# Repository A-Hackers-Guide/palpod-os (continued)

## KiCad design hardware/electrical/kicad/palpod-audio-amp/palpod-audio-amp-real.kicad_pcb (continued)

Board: 6 copper layers, 73 parts (0 on the bottom side), 78 nets, no tracks yet.

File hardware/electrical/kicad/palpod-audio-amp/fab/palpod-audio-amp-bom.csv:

"Refs","Value","Footprint","Qty","DNP"
"A13","1ET7040SA_TWEETER","palpod-audio-amp:Purifi_1ET7040SA_Module","1",""
"A14","1ET7040SA_MID","palpod-audio-amp:Purifi_1ET7040SA_Module","1",""
"A15","1ET7040SA_WOOFER","palpod-audio-amp:Purifi_1ET7040SA_Module","1",""
"A16","1ET7040SA_SUBWOOFER","palpod-audio-amp:Purifi_1ET7040SA_Module","1",""
"C28","100nF","Capacitor_SMD:C_0402_1005Metric","1",""
"C29","100nF","Capacitor_SMD:C_0402_1005Metric","1",""
"C30","100nF","Capacitor_SMD:C_0402_1005Metric","1",""
"C31","100nF","Capacitor_SMD:C_0402_1005Metric","1",""
"C32","100nF","Capacitor_SMD:C_0402_1005Metric","1",""
"C33","100nF","Capacitor_SMD:C_0402_1005Metric","1",""
"C34","100nF","Capacitor_SMD:C_0402_1005Metric","1",""
"C35","100nF","Capacitor_SMD:C_0402_1005Metric","1",""
"C36","100nF","Capacitor_SMD:C_0402_1005Metric","1",""
"C37","100nF","Capacitor_SMD:C_0402_1005Metric","1",""
"C38","100nF","Capacitor_SMD:C_0402_1005Metric","1",""
"C39","100nF","Capacitor_SMD:C_0402_1005Metric","1",""
"C40","100nF","Capacitor_SMD:C_0402_1005Metric","1",""
"C41","100nF","Capacitor_SMD:C_0402_1005Metric","1",""
"C42","100nF","Capacitor_SMD:C_0402_1005Metric","1",""
"C43","100nF","Capacitor_SMD:C_0402_1005Metric","1",""
"C44","100nF","Capacitor_SMD:C_0402_1005Metric","1",""
"C45","100nF","Capacitor_SMD:C_0402_1005Metric","1",""
"C46","100nF","Capacitor_SMD:C_0402_1005Metric","1",""
"C47","100nF","Capacitor_SMD:C_0402_1005Metric","1",""
"C48","100nF","Capacitor_SMD:C_0402_1005Metric","1",""
"C49","100nF","Capacitor_SMD:C_0402_1005Metric","1",""
"C50","100nF","Capacitor_SMD:C_0402_1005Metric","1",""
"C51","100nF","Capacitor_SMD:C_0402_1005Metric","1",""
"C52","10uF","Capacitor_SMD:C_0805_2012Metric","1",""
"C53","10uF","Capacitor_SMD:C_0805_2012Metric","1",""
"C54","10uF","Capacitor_SMD:C_0805_2012Metric","1",""
"C55","10uF","Capacitor_SMD:C_0805_2012Metric","1",""
"C56","10uF","Capacitor_SMD:C_0805_2012Metric","1",""
"C57","10uF","Capacitor_SMD:C_0805_2012Metric","1",""
"C58","10uF","Capacitor_SMD:C_0805_2012Metric","1",""
"C59","10uF","Capacitor_SMD:C_0805_2012Metric","1",""
"C60","1000uF/100V","Capacitor_THT:CP_Radial_D18.0mm_P7.50mm","1",""
"C61","1000uF/100V","Capacitor_THT:CP_Radial_D18.0mm_P7.50mm","1",""
"C62","1000uF/100V","Capacitor_THT:CP_Radial_D18.0mm_P7.50mm","1",""
"C63","1000uF/100V","Capacitor_THT:CP_Radial_D18.0mm_P7.50mm","1",""
"J1","PSU_INPUT","TerminalBlock:TerminalBlock_bornier-4_P5.08mm","1",""
"J2","I2S_DSD_IN","Connector_PinHeader_2.54mm:PinHeader_1x04_P2.54mm_Vertical","1",""
"J24","SPKR_TWEETER","palpod-audio-amp:WBT-0705_Terminal","1",""
"J25","SPKR_MID","palpod-audio-amp:WBT-0705_Terminal","1",""
"J26","SPKR_WOOFER","palpod-audio-amp:WBT-0705_Terminal","1",""
"J27","SPKR_SUBWOOFER","palpod-audio-amp:WBT-0705_Terminal","1",""
"L72","22uH","Inductor_SMD:L_Coilcraft_XAL1010","1",""
"L73","22uH","Inductor_SMD:L_Coilcraft_XAL1010","1",""
"R64","4.7k","Resistor_SMD:R_0402_1005Metric","1",""
"R65","4.7k","Resistor_SMD:R_0402_1005Metric","1",""
"R66","4.7k","Resistor_SMD:R_0402_1005Metric","1",""
"R67","4.7k","Resistor_SMD:R_0402_1005Metric","1",""
"R68","4.7k","Resistor_SMD:R_0402_1005Metric","1",""
"R69","4.7k","Resistor_SMD:R_0402_1005Metric","1",""
"R70","4.7k","Resistor_SMD:R_0402_1005Metric","1",""
"R71","4.7k","Resistor_SMD:R_0402_1005Metric","1",""
"U3","CS2100-CP","palpod-audio-amp:CS2100_MSOP10","1",""
"U4","Si8660BB-B-IS1","palpod-audio-amp:Si8660_SOIC16","1",""
"U5","CS43198_TWEETER","palpod-audio-amp:CS43198_TQFN32","1",""
"U6","CS43198_MID","palpod-audio-amp:CS43198_TQFN32","1",""
"U7","CS43198_WOOFER","palpod-audio-amp:CS43198_TQFN32","1",""
"U8","CS43198_SUBWOOFER","palpod-audio-amp:CS43198_TQFN32","1",""
"U9","THAT1512_TWEETER","palpod-audio-amp:THAT1512_SOIC8","1",""
"U10","THAT1512_MID","palpod-audio-amp:THAT1512_SOIC8","1",""
"U11","THAT1512_WOOFER","palpod-audio-amp:THAT1512_SOIC8","1",""
"U12","THAT1512_SUBWOOFER","palpod-audio-amp:THAT1512_SOIC8","1",""
"U17","LM5116MHX_PLUS60V","palpod-audio-amp:LM5116_HTSSOP24","1",""
"U18","LM5116MHX_MINUS60V","palpod-audio-amp:LM5116_HTSSOP24","1",""
"U19","TPS3808G01DBVR","palpod-audio-amp:TPS3808_SOT23-5","1",""
"U20","ADT7420_TWEETER","palpod-audio-amp:ADT7420_MSOP8","1",""
"U21","ADT7420_MID","palpod-audio-amp:ADT7420_MSOP8","1",""
"U22","ADT7420_WOOFER","palpod-audio-amp:ADT7420_MSOP8","1",""
"U23","ADT7420_SUBWOOFER","palpod-audio-amp:ADT7420_MSOP8","1",""

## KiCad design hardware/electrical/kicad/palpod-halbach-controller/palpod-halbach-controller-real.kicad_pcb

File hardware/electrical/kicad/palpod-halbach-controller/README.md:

# Hearth Halbach Levitation Controller — KiCad Project

**SAFETY-CRITICAL BOARD.** This is the real-time active stabilization
controller for the Halbach neodymium levitation array that holds the OLED orb
in front of the column. A control failure means a 2 kg glass sphere becomes a
projectile aimed at the user's rug (or foot). Treat every net, every symbol,
and every layout decision on this board as safety-critical until proven
otherwise via FMEA.

> ⚠️  **SAFETY REVIEW REQUIRED BEFORE POWER-ON.** Before energizing the 48 V
> coil rail for the first time — even on the bench — a licensed EE must sign
> off on the following in writing:
>
> 1. **Overcurrent latch verified.** TL331 (`U4`) trips the DRV8323 nFAULT
>    line when the summed INA240 output exceeds the hardware threshold
>    (target 30 A per phase). Bench-verify with a current-limited supply and
>    a scope; do not rely on datasheet values.
> 2. **Watchdog window verified.** MAX706 (`U3`) issues RESETn if the primary
>    STM32H723 misses a WDI pet in the 100 ms window. Firmware halts must be
>    provably caught in < 110 ms end-to-end.
> 3. **E-stop opens the coil rail in < 10 ms.** The rear-panel E-stop must
>    drive the MAX706 MR pin *and* an in-line contactor on the 48 V rail —
>    software must not be in the critical path. Latching; reset requires
>    physical button press.
> 4. **Lockstep pair agrees.** Both `U1` and `U2` (STM32H723ZGT6) compute the
>    same servo output every 100 µs; disagreement > tolerance latches
>    SAFE-SHUTDOWN (coils de-energize, catch-net engages, orb comes down
>    controlled).
> 5. **Drop-catch net installed.** The internal catch-net inside the column
>    is present and rated for the orb's terminal drop energy from full
>    levitation height.
> 6. **Magnetic-field survey.** Exterior surface field < 100 µT at maximum
>    coil current per ICNIRP 2020 general-public reference levels. Test with
>    a Narda ELT-400 or equivalent.
> 7. **Pacemaker / ISO 7010 W006 warning label** applied to the column at
>    the top plate and included in the setup manual.

See `../../block-diagrams/levitation-controller.md` for the system-level
control loop, latency budget, fault-response matrix, and regulatory notes.

## How to open

Requires **KiCad 8.0.0 or later** (KiCad 9 and 10 also open cleanly;
we developed and validated against KiCad 10.0.5 on macOS).

```
open -a KiCad /private/tmp/claude-501/-Users-lexer-kindle/80e67baf-6192-4db2-b491-aa5b4ee00c5b/scratchpad/palpod-os/hardware/electrical/kicad/palpod-halbach-controller/palpod-halbach-controller.kicad_pro
```

Or double-click `palpod-halbach-controller.kicad_pro` in Finder. From KiCad's
project manager, open **Schematic Editor** and **PCB Editor**.

Project-local symbol and footprint libraries live in `libraries/`; the
`sym-lib-table` and `fp-lib-table` at the project root register them under the
alias `palpod-halbach-controller`. Standard KiCad symbols (`Device:R`,
`Device:C`, `power:*`) are embedded in the schematic's `lib_symbols` block so
the schematic opens even on a fresh KiCad install that has not yet configured
its stock libraries.

## What's populated

- [x] `.kicad_pro`: 4-layer stackup, ENIG, JLCPCB-friendly minimums, and
      **five net classes**:
    - `Default` — 0.2 mm signal
    - `Power` — 0.5 mm rails
    - `COIL_HIGH_CURRENT` — **5.0 mm min width, 2.0 mm vias**, orange in
      the PCB editor; auto-assigned to `COIL_*`, `PHASE_*`, `PVDD`, `PGND`.
    - `CAN_FD_DIFF` — 100 Ω differential CAN-FD pair (`CANH`/`CANL`)
    - `SAFETY_CRITICAL` — pink; auto-assigned to `ESTOP*`, `OC_LATCH*`,
      `WDOG*`, `nFAULT*`, `LOCKSTEP*`
- [x] `.kicad_sch` root schematic on A2 with populated title block
      (rev A0, 2026-08-03), embedded `lib_symbols` for every reference used.
- [x] Placed symbols:
    - 2× STM32H723ZGT6 (`U1` primary, `U2` redundant) — the lockstep pair
    - 1× MAX706 window watchdog supervisor (`U3`)
    - 1× TL331 hardware overcurrent comparator (`U4`)
    - 1× MCP2542FD CAN-FD transceiver (`U5`)
    - 1× STM32G030K8T6 aux housekeeping MCU (`U6`)
    - 6× MLX90393 3D hall-effect sensors (`U7`…`U12`)
    - 6× DRV8323 gate drivers (`U13`…`U18`)
    - 12× IPI050N06N MOSFETs (`Q1`…`Q12`) — one half-bridge per driver
    - 6× INA240 current-sense amps (`U25`…`U30`)
    - 1× Recom RTK-2412 isolated DC-DC brick (`U10`) for driver rail
      isolation
    - Bulk + local decoupling capacitors, shunt resistors, pull-ups
    - Power flags: `+48V`, `+12V`, `+5V`, `+3V3`, `GND`, `GNDA`, `PGND`
- [x] Three big red-bordered safety-callout banners on the schematic
      explicitly labeling the `OC_LATCH`, `ESTOP_LATCH`, and `LOCKSTEP_A/B`
      net groups as `SAFETY-CRITICAL — DO NOT REMOVE`.
- [x] Illustrative wires and 40+ pre-placed labels seeding the wiring
      pattern: `LOCKSTEP_A_MOSI/MISO/SCK`, `LOCKSTEP_B_MOSI/MISO/SCK`,
      `WDOG_WDI`, `WDOG_RESETn`, `ESTOP_LATCH`, `ESTOP_IN`, `OC_LATCH`,
      `OC_SUM_IN`, `CAN_TXD`, `CAN_RXD`, `CANH`, `CANL`,
      `HALL0_SDA` … `HALL5_DRDY`, `COIL_1_HIGH` … `COIL_6_LOW`,
      `OC_CH1` … `OC_CH6`.
- [x] `no_connect` flags on illustrative test pins.
- [x] `libraries/palpod-halbach-controller.kicad_sym` — hand-drawn symbols
      for **10 specialty parts**: STM32H723ZGT6 (LQFP-144), DRV8323
      (HTSSOP-48 EP), INA240 (TSSOP-8), MLX90393 (QFN-16), MAX706 (SO-8),
      MCP2542FD (SO-8), TL331 (SOT-23-5), IPI050N06N (TO-262), STM32G030K8T6
      (LQFP-32), RTK-2412 (SIP-4). **Pin mappings are placeholder
      groupings — the EE must verify each pin against the manufacturer
      datasheet before wiring.**
- [x] `libraries/palpod-halbach-controller.pretty/` — twelve placeholder
      footprints. See `libraries/palpod-halbach-controller.pretty/README.md`
      for per-part verification checklist.
- [x] `.kicad_pcb`: 4-layer stackup declared
      (`F.Cu` signal 2 oz / `In1.Cu` GND 1 oz / `In2.Cu` PWR_HIGH_CURRENT
      1 oz / `B.Cu` signal 2 oz), 1.6 mm total, ENIG finish.
      **150 × 100 mm rectangular Edge.Cuts** drawn. Silkscreen and
      SAFETY.Callouts (`User.1`) layer notes populated. No footprints placed
      yet — the EE places them during layout.
- [x] `sym-lib-table` / `fp-lib-table` register the project-local
      `palpod-halbach-controller` library.

## What's stubbed / next steps for the EE

- [ ] **Verify placeholder footprints against real datasheets** before ordering
      fab. See `libraries/palpod-halbach-controller.pretty/README.md`. The
      MOSFET and DRV8323 placeholders in particular are safety-critical — a
      wrong pad on the current-sense pins would defeat the OC latch.
- [ ] **Verify placeholder pin mappings** on all specialty symbols against the
      manufacturer datasheets. Update
      `libraries/palpod-halbach-controller.kicad_sym` with correct pin numbers,
      names, and electrical types.
- [ ] **Complete the schematic wiring** — this is a placeholder; the EE draws
      the actual nets. Priorities in this order:
    1. **Lockstep interconnect** (`U1` ↔ `U2` SPI cross-strap) — this is what
       makes the board single-fault tolerant.
    2. **OC latch chain** — 6× INA240 outputs sum into TL331 (`U4`) input,
       comparator output latches through an SR flip-flop, drives all
       DRV8323 nENABLE lines low. Independent of MCU firmware.
    3. **Watchdog chain** — U1 pets MAX706 WDI; MAX706 RESETn drives an
       AND gate on the enable path.
    4. **E-stop chain** — hardwired E-stop input → MAX706 MR → coil-rail
       contactor coil. Two-channel, redundant per SIL-2 practice.
    5. **CAN-FD bus** — U1/U2 FDCAN1 → MCP2542FD → CANH/CANL termination
       (120 Ω split-terminate at each end of the bus).
    6. **Hall sensor bus** — I2C bus (with per-sensor A0/A1 straps for
       unique addresses) or SPI daisy-chain from U1. Route as star from
       the MCU quadrant; twist pairs on the flex cable side.
    7. **6× DRV8323 SPI config + PWM** — SPI shared, 6× nSCS individual;
       6× (INHA/INLA/INHB/INLB/INHC/INLC) from timer channels.
    8. **48 V rail** — 12 V input → RTK-2412 isolation → LM5155 boost →
       coil rail. Bulk 470 µF / 100 V polymer at each DRV8323 PVDD pin
       plus one 1 mF electrolytic per pair.
    9. **Power tree** — 12 V → 5 V (LMR33630) → 3.3 V (TPS7A20) for logic;
       separate 3.3 V analog rail (`+3V3A`) for INA240 REF pins.
    10. **Decoupling** — 100 nF within 3 mm of every power pin; add
        4.7 µF bulk per rail per IC.
- [ ] Add ESD protection on the E-stop input (`PESD5V0L1BA`) and the CAN
      bus (`PSD03C-LF`).
- [ ] Add optional galvanic isolation on the CAN bus if the main-compute
      board runs on a different ground reference.
- [ ] Assign every schematic symbol a valid footprint (Tools → Assign
      Footprints). Cross-check each MOSFET pad against the datasheet
      before assigning.
- [ ] Update the PCB from the schematic (Tools → Update PCB from Schematic
      in the PCB editor).
- [ ] Place footprints on the 150 × 100 mm board:
    - **Coil-driver quadrant** on the right half of the board with the
      six DRV8323 + MOSFET pairs in a row along the top edge; INA240
      shunt-amps immediately downstream; 2-pin screw terminals for the
      coil outputs on the right board edge.
    - **MCU quadrant** on the left half; lockstep pair placed
      symmetrically about the vertical midline to keep cross-strap
      trace lengths matched.
    - **MAX706 + TL331 + estop terminal + fault-latch logic** in the
      bottom-center, straddling the moat between quadrants.
    - **CAN-FD transceiver + connector** on the left edge.
    - **Hall-sensor flex connectors** across the bottom edge (6× JST-PH
      or FPC, TBD by mechanical team).
- [ ] Pour GND (`In1.Cu`) — split zone with a **moat between the
      analog/logic and coil-driver domains**, tied at a single point near
      the ADC reference.
- [ ] Pour high-current PWR (`In2.Cu`) — divide into 48 V, 12 V, and 5 V
      zones; use polygon copper for the 48 V zone in the coil-driver
      quadrant. Target 5 mm min width on all `COIL_HIGH_CURRENT` traces on
      outer layers (2 oz copper handles ~30 A at this width with modest
      temperature rise).
- [ ] Route CAN-FD as a 100 Ω differential pair. Route lockstep SPI as
      length-matched pair between the two MCUs.
- [ ] Run ERC (`kicad-cli sch erc` or Tools → Electrical Rules Checker) —
      the placeholder generates violations; drive them to zero.
- [ ] Run DRC (`kicad-cli pcb drc` or Tools → Design Rules Checker) to
      zero, including `SAFETY_CRITICAL` clearance = 0.4 mm.
- [ ] **Formal design review** with a second EE (independent of the
      designer) covering the safety chain, current paths, and layout of
      the OC / WDT / lockstep / e-stop nets.
- [ ] **FMEA / DFMEA** covering every failure mode in the fault-response
      matrix in `levitation-controller.md`.
- [ ] Generate Gerbers + drill + BOM + pick-and-place
      (`File → Fabrication Outputs`). Cross-check the BOM against the block
      diagram.
- [ ] Order 5-unit proto run from JLCPCB (4-layer, 2 oz outer, ENIG,
      ~2-week turn).

## Command-line validation

The project has been validated with `kicad-cli` 10.0.5:

```
kicad-cli sch export netlist -o /tmp/palpod-halbach.net palpod-halbach-controller.kicad_sch
kicad-cli pcb export gerbers -o /tmp/g/                 palpod-halbach-controller.kicad_pcb
kicad-cli sym export svg     -o /tmp/sym-svg/           libraries/palpod-halbach-controller.kicad_sym
kicad-cli fp  export svg     -o /tmp/fp-svg/            libraries/palpod-halbach-controller.pretty
```

## File format

- Schematic schema version `20231120` (KiCad 8)
- PCB schema version `20240108` (KiCad 8)
- Symbol library schema version `20231120`
- Footprint schema version `20240108`

Written in the `(hide yes)` effect-block form so the same files load
identically under KiCad 8, 9, and 10.

## Certifications targeted (product-level, not board-level)

- **UL 60335** (Household and similar electrical appliances — Safety) for
  the appliance as a whole.
- **FCC Part 15** subpart B (unintentional radiator) — switching noise from
  the DRV8323 stage is the primary risk. Add pre-compliance scanning as
  early as possible.
- **ICNIRP 2020** general-public magnetic-field reference levels — verify
  at the column exterior surface under worst-case coil current.
- **FDA notice for magnetic-field-near-pacemaker** — product-level, not
  board-level, but the PCB silkscreen carries the ISO 7010 W006 icon.

## Reference

- **System-level block diagram, latency budget, fault-response matrix:**
  `../../block-diagrams/levitation-controller.md`

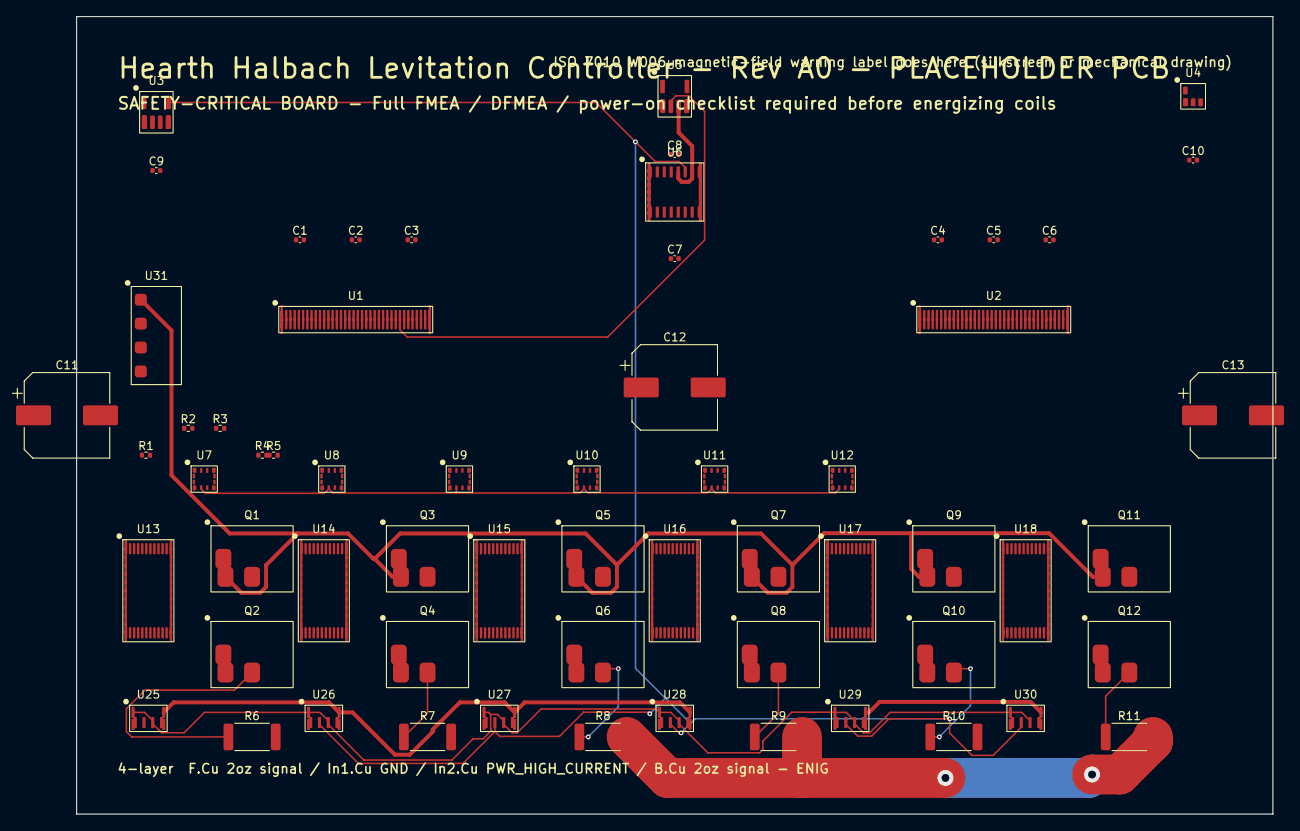
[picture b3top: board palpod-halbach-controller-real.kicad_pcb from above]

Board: 4 copper layers, 150.0 x 100.0 mm, 61 parts (0 on the bottom side), 67 nets.

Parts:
C1, C2, C3, C4, C5, C6, C7, C8, C9, C10: 100nF; C_0402_1005Metric
C11, C12, C13: 220uF; CP_Elec_10x10.5
Q1, Q2, Q3, Q4, Q5, Q6, Q7, Q8, Q9, Q10, Q11, Q12: IPI050N06N; TO-262-3_TabPin2
R1, R2, R3, R4, R5: 10k; R_0402_1005Metric
R6, R7, R8, R9, R10, R11: 0R005 5W; R_2512_6332Metric
U1: STM32H723ZGT6 (Primary); LQFP-144_20x20mm_P0.5mm
U2: STM32H723ZGT6 (Redundant); LQFP-144_20x20mm_P0.5mm
U3: MAX706; SOIC-8_3.9x4.9mm_P1.27mm
U4: TL331; SOT-23-5
U5: MCP2542FD; SOIC-8_3.9x4.9mm_P1.27mm
U6: STM32G030K8T6; LQFP-32_7x7mm_P0.8mm
U7: MLX90393 #1; QFN-16_3x3mm_P0.5mm
U8: MLX90393 #2; QFN-16_3x3mm_P0.5mm
U9: MLX90393 #3; QFN-16_3x3mm_P0.5mm
U10: MLX90393 #4; QFN-16_3x3mm_P0.5mm
U11: MLX90393 #5; QFN-16_3x3mm_P0.5mm
U12: MLX90393 #6; QFN-16_3x3mm_P0.5mm
U13: DRV8323 CH1; HTSSOP-48_6.1x12.5mm_P0.5mm_EP
U14: DRV8323 CH2; HTSSOP-48_6.1x12.5mm_P0.5mm_EP
U15: DRV8323 CH3; HTSSOP-48_6.1x12.5mm_P0.5mm_EP
U16: DRV8323 CH4; HTSSOP-48_6.1x12.5mm_P0.5mm_EP
U17: DRV8323 CH5; HTSSOP-48_6.1x12.5mm_P0.5mm_EP
U18: DRV8323 CH6; HTSSOP-48_6.1x12.5mm_P0.5mm_EP
U25, U26, U27, U28, U29, U30: INA240; TSSOP-8_4.4x3mm_P0.65mm
U31: RTK-2412; SIP-4_Recom_RTK

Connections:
+3V3: U5.5, U6.26, U6.28, U7.2, U8.2, U9.2, U10.2, U11.2, U12.2, U13.13, U13.15, U14.13, U14.15, U15.13, U15.15, U16.13, U16.15, U17.13, U17.15, U18.13, U18.15
+5V: U3.7, U5.3, U25.8, U26.8, U27.8, U28.8, U29.8, U30.8
+12V: U4.5, U13.38, U14.38, U15.38, U16.38, U17.38, U18.38
+48V: Q1.2, Q3.2, Q5.2, Q7.2, Q9.2, Q11.2, U13.37, U14.37, U15.37, U16.37, U17.37, U18.37, U31.1
CAN_RX: U1.33, U5.4
CAN_TX: U1.64, U5.1
COIL_0_HIGH_A: Q1.1, U1.65, U13.1, U13.25
COIL_0_HIGH_B: U2.65, U13.3, U13.28
COIL_0_LOW_A: Q2.1, U1.71, U13.2, U13.27
COIL_0_LOW_B: U2.71, U13.4, U13.30
COIL_1_HIGH_A: Q3.1, U1.66, U14.1, U14.25
COIL_1_HIGH_B: U2.66, U14.3, U14.28
COIL_1_LOW_A: Q4.1, U1.72, U14.2, U14.27
COIL_1_LOW_B: U2.72, U14.4, U14.30
COIL_2_HIGH_A: Q5.1, U1.67, U15.1, U15.25
COIL_2_HIGH_B: U2.67, U15.3, U15.28
COIL_2_LOW_A: Q6.1, U1.73, U15.2, U15.27
COIL_2_LOW_B: U2.73, U15.4, U15.30
COIL_3_HIGH_A: Q7.1, U1.68, U16.1, U16.25
COIL_3_HIGH_B: U2.68, U16.3, U16.28
COIL_3_LOW_A: Q8.1, U1.74, U16.2, U16.27
COIL_3_LOW_B: U2.74, U16.4, U16.30
COIL_4_HIGH_A: Q9.1, U1.69, U17.1, U17.25
COIL_4_HIGH_B: U2.69, U17.3, U17.28
COIL_4_LOW_A: Q10.1, U1.75, U17.2, U17.27
COIL_4_LOW_B: U2.75, U17.4, U17.30
COIL_5_HIGH_A: Q11.1, U1.70, U18.1, U18.25
COIL_5_HIGH_B: U2.70, U18.3, U18.28
COIL_5_LOW_A: Q12.1, U1.76, U18.2, U18.27
COIL_5_LOW_B: U2.76, U18.4, U18.30
CS_0: U1.49, U7.9
CS_1: U1.50, U8.9
CS_2: U1.51, U9.9
CS_3: U1.52, U10.9
CS_4: U1.53, U11.9
CS_5: U1.54, U12.9
ESTOP_LATCH: U1.62, U2.62, U3.1
GND: U3.8, U4.2, U5.2, U6.27, U7.13, U8.13, U9.13, U10.13, U11.13, U12.13, U13.14, U14.14, U15.14, U16.14, U17.14, U18.14, U25.4, U26.4, U27.4, U28.4, U29.4, U30.4
GNDA: U25.1, U25.5, U26.1, U26.5, U27.1, U27.5, U28.1, U28.5, U29.1, U29.5, U30.1, U30.5
ISENSE_0: U1.1, U25.6
ISENSE_1: U1.2, U26.6
ISENSE_2: U1.3, U27.6
ISENSE_3: U1.4, U28.6
ISENSE_4: U1.5, U29.6
ISENSE_5: U1.6, U30.6
LOCKSTEP_A: U1.60, U2.60
LOCKSTEP_B: U1.61, U2.61
OCP_SUM: U4.4, U25.7, U26.7, U27.7, U28.7, U29.7, U30.7
OC_LATCH: U1.58, U2.58, U4.1, U13.8, U14.8, U15.8, U16.8, U17.8, U18.8
PGND: R6.2, R7.2, R8.2, R9.2, R10.2, R11.2, U13.39, U14.39, U15.39, U16.39, U17.39, U18.39, U25.2, U26.2, U27.2, U28.2, U29.2, U30.2
PHASE_0: Q1.3, Q2.2, U13.26
PHASE_1: Q3.3, Q4.2, U14.26
PHASE_2: Q5.3, Q6.2, U15.26
PHASE_3: Q7.3, Q8.2, U16.26
PHASE_4: Q9.3, Q10.2, U17.26
PHASE_5: Q11.3, Q12.2, U18.26
SHUNT_HI_0: Q2.3, R6.1, U25.3
SHUNT_HI_1: Q4.3, R7.1, U26.3
SHUNT_HI_2: Q6.3, R8.1, U27.3
SHUNT_HI_3: Q8.3, R9.1, U28.3
SHUNT_HI_4: Q10.3, R10.1, U29.3
SHUNT_HI_5: Q12.3, R11.1, U30.3
SPI_MISO: U1.57, U7.6, U8.6, U9.6, U10.6, U11.6, U12.6
SPI_MOSI: U1.56, U7.5, U8.5, U9.5, U10.5, U11.5, U12.5
SPI_SCLK: U1.55, U7.4, U8.4, U9.4, U10.4, U11.4, U12.4
WDOG_KICK: U1.59, U2.59, U3.4
WDT_OUT: U1.63, U2.63, U3.3
